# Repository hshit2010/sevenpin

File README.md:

# seven pin

Hi my name is harshit and i started this project 3 days ago with no knowledge of hardware etc and this journey took 3 days in short like this 
day1: created the schematic, pcb design 
day 2: completed the pcb and started on case 
day 3:completed the case 
in this project i have 6 keys , rotatory dial and 1 mini oled screen used 

## hardware
it has Seeed Studio XIAO RP2040 as the main microcontroller

## firmware structure

it uses KMK and is structured like this :

-SW1: Copy (Ctrl+C)

-SW2: Paste (Ctrl+V)

-SW3: Cut (Ctrl+X)

-SW4: Undo (Ctrl+Z)

-SW5: Save (Ctrl+S)

-SW6: Select All (Ctrl+A)

-Dial: Volume Up / Down & Mute

## softwares used:
1) kicad for pcb schematic and design
2) fusion360 for case design
3) vs code and kmk KMK to write the firmware

## licence
MIT

## installation
you can install this by clicking on the big green code button and then clicking "download as ZIP"

## 3D Case Design & Assembly

## Case layout 

## PCB Layout

## Schematic

## Bill of Materials (BOM)

`| Item |                                     |Quantity | Description |`

`| :--- | :--- | :--- |`

`| Seeed Studio XIAO RP2040                   | 1 | Main microcontroller board |`

`| Mechanical Switches (Cherry MX style)      | 6 | Key switches |`

`| Rotary Encoder (EC11)                      | 1 | Encoder with push button |`

`| 0.91" I2C OLED Display                     | 1 | 128x32 display module |`

`| 1x4 Female Header Pin Socket               | 1 | 2.54mm socket for OLED |`

`| 3D Printed Case Parts                      | 1 Set | Top plate, middle walls, bottom plate |`

`| M2 / M3 Screws                             | 4 | Case assembly fasteners |`

---

hope you will love it ;)

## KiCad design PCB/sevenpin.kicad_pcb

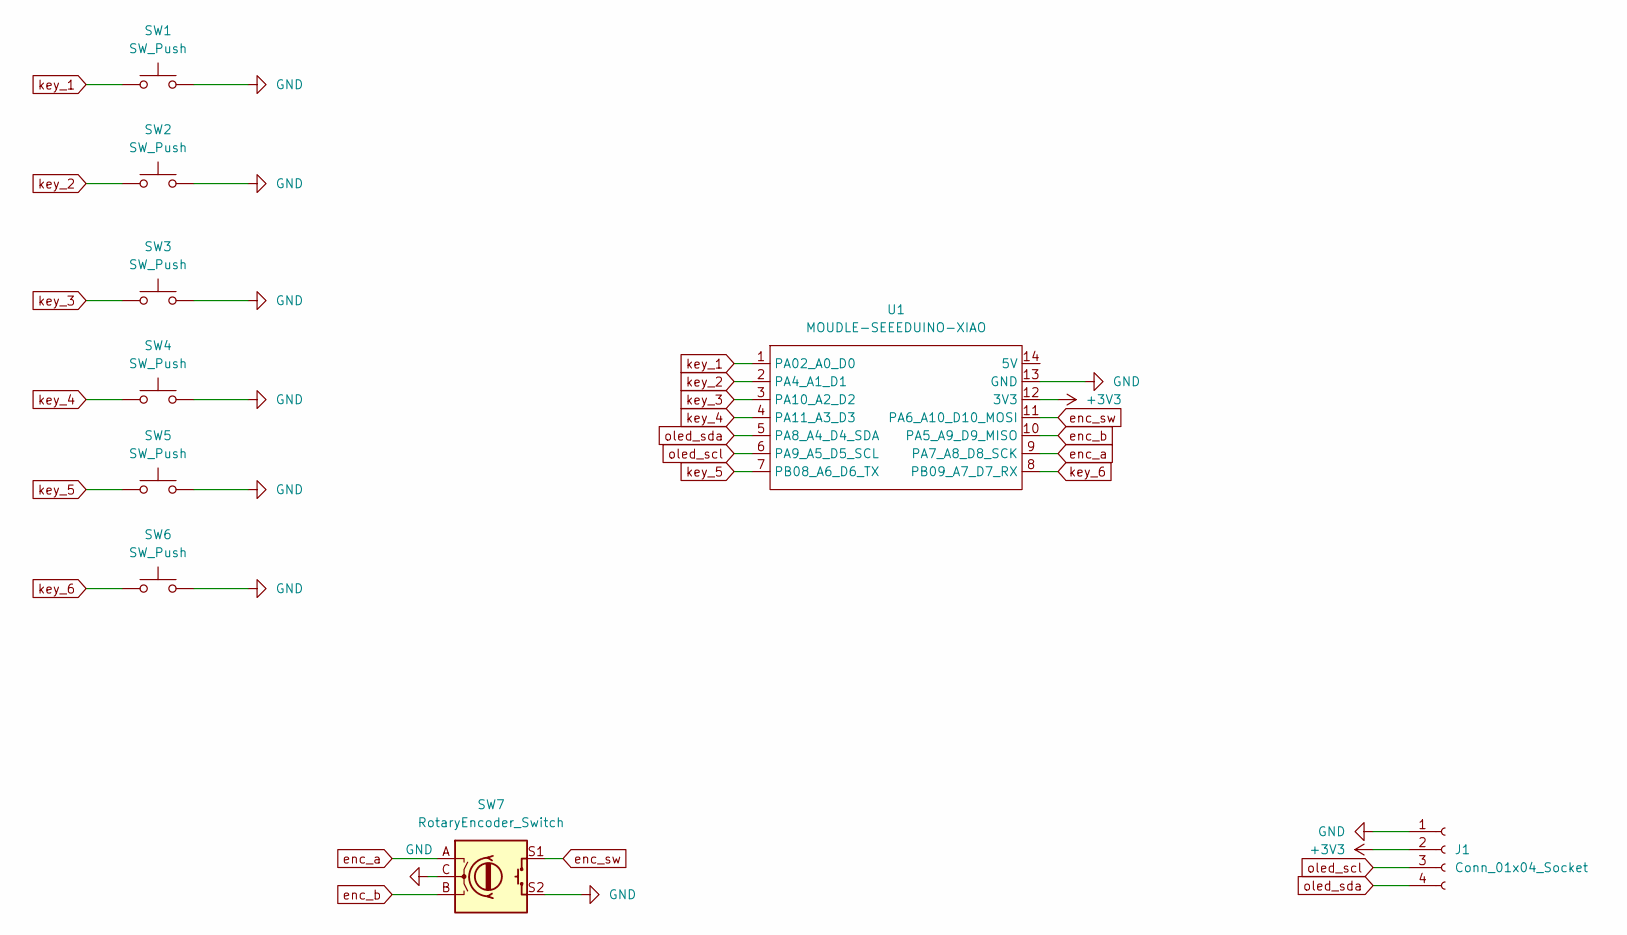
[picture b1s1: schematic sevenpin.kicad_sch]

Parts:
J1: Conn_01x04_Socket; PinSocket_1x04_P2.54mm_Vertical
SW1, SW2, SW3, SW4, SW5, SW6: SW_Push; SW_Cherry_MX_1.00u_PCB
SW7: RotaryEncoder_Switch; RotaryEncoder_Alps_EC11E-Switch_Vertical_H20mm
U1: MOUDLE-SEEEDUINO-XIAO; XIAO-Generic-Hybrid-14P-2.54-21X17.8MM

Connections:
+3V3: J1.2, U1.12 (3V3)
GND: J1.1, SW1.2, SW2.2, SW3.2, SW4.2, SW5.2, SW6.2, SW7.C, SW7.S2, U1.13 (GND)
enc_a: SW7.A, U1.9 (PA7_A8_D8_SCK)
enc_b: SW7.B, U1.10 (PA5_A9_D9_MISO)
enc_sw: SW7.S1, U1.11 (PA6_A10_D10_MOSI)
key_1: SW1.1, U1.1 (PA02_A0_D0)
key_2: SW2.1, U1.2 (PA4_A1_D1)
key_3: SW3.1, U1.3 (PA10_A2_D2)
key_4: SW4.1, U1.4 (PA11_A3_D3)
key_5: SW5.1, U1.7 (PB08_A6_D6_TX)
key_6: SW6.1, U1.8 (PB09_A7_D7_RX)
oled_scl: J1.3, U1.6 (PA9_A5_D5_SCL)
oled_sda: J1.4, U1.5 (PA8_A4_D4_SDA)

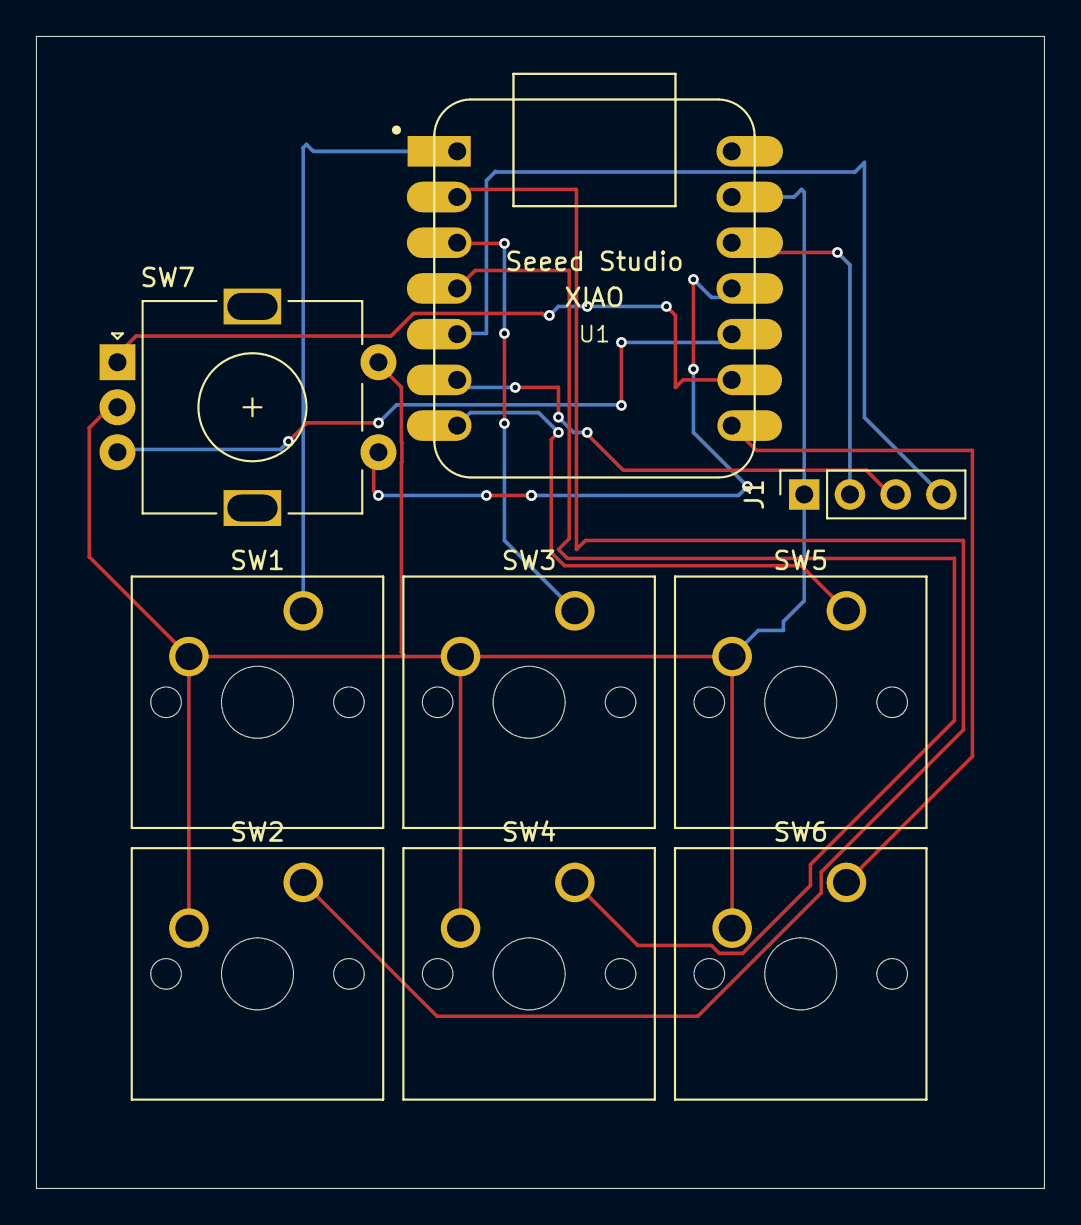
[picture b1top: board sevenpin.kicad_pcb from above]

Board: 2 copper layers, 56.0 x 64.0 mm, 9 parts (0 on the bottom side), 13 nets.
